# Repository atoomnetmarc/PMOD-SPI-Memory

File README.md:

This is a SPI PMOD board and holds your SPI memory chip.

Typical footprints used for SPI memory like DIP-8, SOIC-8 and SOP-8 will fit on the Frankenstein-8 footprint.

*Status*: working.

Tested with:
- APS6404L-3SQR, 8MiB SPI PSRAM
- W25Q64, 8MiB SPI FLASH

My [Kicad library](https://github.com/atoomnetmarc/ATOOMNETKICAD) is used in this project.

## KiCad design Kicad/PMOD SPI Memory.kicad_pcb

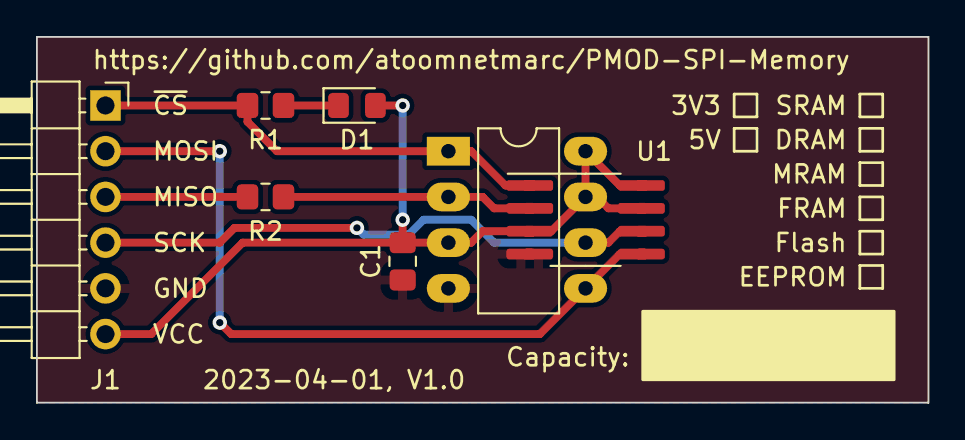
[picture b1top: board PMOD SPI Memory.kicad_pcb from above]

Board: 2 copper layers, 49.5 x 20.3 mm, 6 parts (0 on the bottom side), 8 nets.

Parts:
C1: 100n; C_0805_2012Metric_Pad1.18x1.45mm_HandSolder
D1: Blue; LED_0805_2012Metric_Pad1.15x1.40mm_HandSolder
J1: Pmod peripheral SPI; PinHeader_1x06_P2.54mm_Horizontal
R1: 1k; R_0805_2012Metric_Pad1.20x1.40mm_HandSolder
R2: 100R; R_0805_2012Metric_Pad1.20x1.40mm_HandSolder
U1: SPI Memory; Frankenstein-8

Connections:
+3V3: C1.1, D1.2 (A), J1.6 (VCC), U1.3 (~WP/IO2), U1.7 (~HOLD/IO3), U1.8 (VCC)
GND: C1.2, J1.5 (GND), U1.4 (GND)
MISO: R2.2, U1.2 (DO/IO1)
MOSI: J1.2 (MOSI), U1.5 (DI/IO0)
unnamed: D1.1 (K), R1.1
unnamed: J1.3 (MISO), R2.1
SCK: J1.4 (SCK), U1.6 (CLK)
~CS: J1.1 (~CS), R1.2, U1.1 (~CS)

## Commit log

2023-03-31 First version of the SPI Memory PMOD.
2023-04-01 Small tweaks.
2023-05-02 Soldered
2024-09-27 It works!
2026-01-23 Add CONTRIBUTING.md

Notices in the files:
Kicad/PMOD SPI Memory.kicad_pcb:
Apache License, version 2.0
README.md:
License: Apache 2.0
